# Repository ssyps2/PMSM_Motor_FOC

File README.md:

## Diode Clamped Converter for Vehicle AC machine Drive

### Aim
The aim of this project is to simulate a 3-Phase Diode Clamped Inverter as a battery connected Permanent Magnet Synchronous Machine (PMSM) drive, and design a PCB to implement a low power version of this type of converter. The control algorithm will be tested in PLECS and eventually implemented in the F28379D micro-controller. Torque, speed, and mechanical position closed loop control of the PMSM motor will be included.

### Simulation
The main topology of the circuit for simulation in the PLECS is shown in Figure below.

### PCB Design
The circuit designed in the simulation will be implemented in a 4-layer Printed Circuit Board (PCB). Surface Mount Technology (SMT) will be applied for more compact layout, higher design flexibility, and reducing the noise interference. The microcontroller is selected to be TI’s LAUNCHXL-F28379D, which is a 32-bit MCU with frequency up to 200MHz and sufficient communication interface (like UART, CAN, I2C) and high-speed PWM channels. Also, current sensor will be used to detect the 3-phase current and sampled by ADC to complete the torque control loop.

The schematic of PCB is shown in Figure below.

The PCB layout is shown in Figrue below.

3D Model:

Diode Clamped Inverter:

### TimeTable

### Proposal
[Final Year Project Proposal - Pengyuan SHU.pdf](https://github.com/ssyps2/PMSM_Motor_FOC/files/14595623/Final.Year.Project.Proposal.-.Pengyuan.SHU.pdf)

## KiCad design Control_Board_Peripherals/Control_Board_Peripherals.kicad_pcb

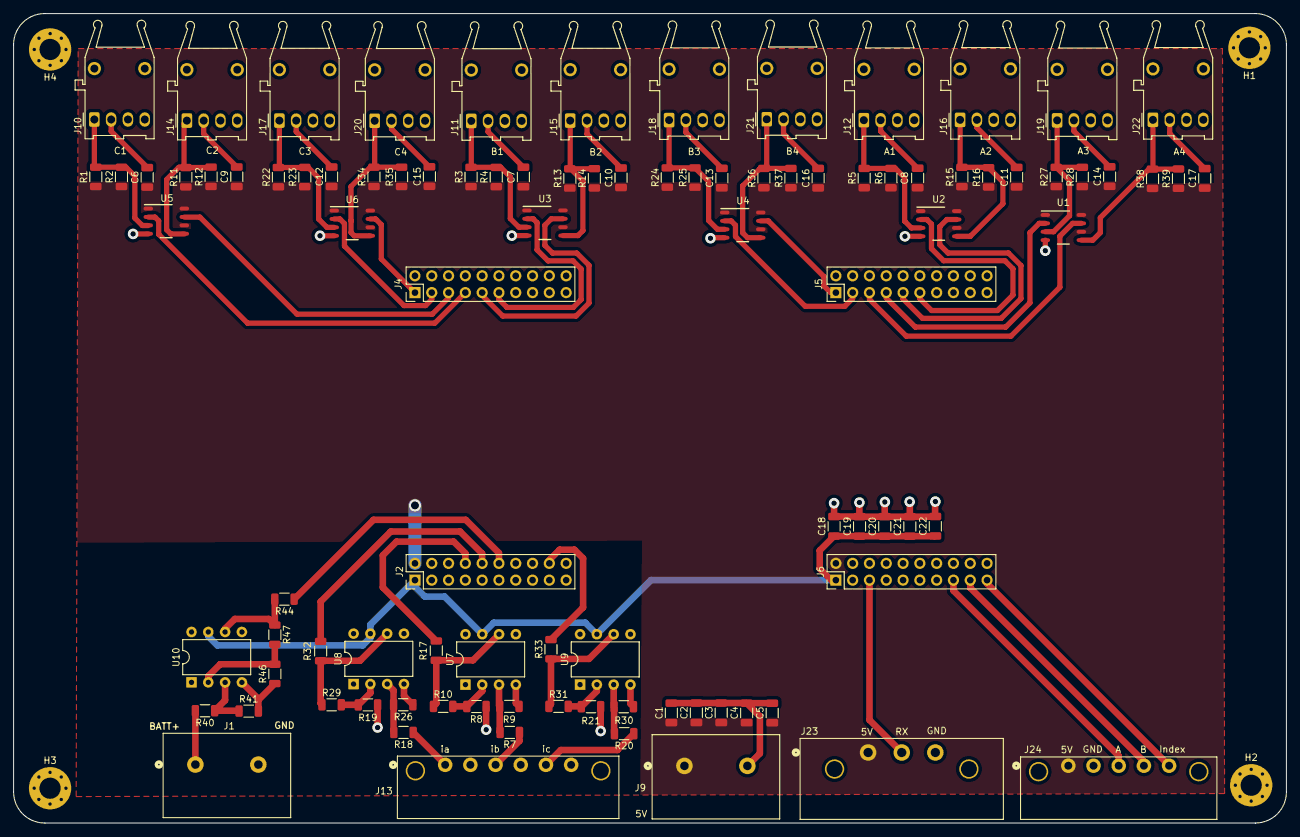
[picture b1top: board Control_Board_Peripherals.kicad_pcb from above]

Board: 2 copper layers, 192.5 x 122.4 mm, 101 parts (0 on the bottom side), 51 nets.

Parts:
C1, C2, C3, C4, C5, C18, C19, C20, C21, C22: 0.1u; C_1206_3216Metric
C6, C7, C8, C9, C10, C11, C12, C13, C14, C15, C16, C17: 4.7u; C_1206_3216Metric
H1, H2, H3, H4: MountingHole; MountingHole_3.2mm_M3_Pad_Via
J1, J9: 1714971; CONN_1714971_PXC
J2, J4, J5, J6: Conn_02x10_Top_Bottom; PinHeader_2x10_P2.54mm_Vertical
J10, J11, J12, J14, J15, J16, J17, J18, J19, J20, J21, J22: HFBR-1521Z; Broadcom_AFBR-16xxZ_Horizontal
J13: 1827907; CONN_1827907
J23: Conn_01x03; CONN_1776511
J24: Conn_01x05; CONN_1827897
R1, R2, R3, R4, R5, R6, R11, R12, R13, R14, R15, R16, R22, R23, R24, R25, R27, R28, R34, R35, R36, R37, R38, R39: 100; R_1206_3216Metric
R7, R18, R20: 5.6k; R_1206_3216Metric
R8, R19, R21: 20k; R_1206_3216Metric
R9, R26, R30: 4.3k; R_1206_3216Metric
R10, R29, R31: 10k; R_1206_3216Metric
R17, R32, R33, R44: 330; R_1206_3216Metric
R40, R46: 100k; R_1206_3216Metric
R41, R47: 1k; R_1206_3216Metric
U1, U2, U3, U4, U5, U6: SN75451BD
U7, U8, U9, U10: TLV2371P; DIP-8_W7.62mm

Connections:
+3.3V: C18.1, C19.1, C20.1, C21.1, C22.1, J2.1, J6.41, U7.7 (V+), U8.7 (V+), U9.7 (V+), U10.7 (V+)
+BATT: J1.1, R40.2
/A1: J5.75, U2.2 (1B)
/A1_In: J12.1 (Data_In), R5.2, R6.2, U2.3 (1Y)
/A2: J5.76, U2.7 (2B)
/A2_In: J16.1 (Data_In), R15.2, R16.2, U2.5 (2Y)
/A3: J5.77, U1.2 (1B)
/A3_In: J19.1 (Data_In), R27.2, R28.2, U1.3 (1Y)
/A4: J5.78, U1.7 (2B)
/A4_In: J22.1 (Data_In), R38.2, R39.2, U1.5 (2Y)
/B1: J4.35 (Pin_5), U3.2 (1B)
/B1_In: J11.1 (Data_In), R3.2, R4.2, U3.3 (1Y)
/B2: J4.36, U3.7 (2B)
/B2_In: J15.1 (Data_In), R13.2, R14.2, U3.5 (2Y)
/B3: J5.79, U4.2 (1B)
/B3_In: J18.1 (Data_In), R24.2, R25.2, U4.3 (1Y)
/B4: J5.80, U4.7 (2B)
/B4_In: J21.1 (Data_In), R36.2, R37.2, U4.5 (2Y)
/C1: J4.37, U5.2 (1B)
/C1_In: J10.1 (Data_In), R1.2, R2.2, U5.3 (1Y)
/C2: J4.38, U5.7 (2B)
/C2_In: J14.1 (Data_In), R11.2, R12.2, U5.5 (2Y)
/C3: J4.39, U6.2 (1B)
/C3_In: J17.1 (Data_In), R22.2, R23.2, U6.3 (1Y)
/C4: J4.40, U6.7 (2B)
/C4_In: J20.1 (Data_In), R34.2, R35.2, U6.5 (2Y)
/CH_A: J6.48, J24.3
/CH_B: J6.49, J24.4
/Index: J6.50, J24.5
/SCIC_RX: J6.43, J23.2
/dc_sample: J2.26, R44.1
/ia_adc: J2.25, R32.1
/ib_adc: J2.24, R17.1
/ic_adc: J2.29, R33.1
GND: C1.2, C2.2, C3.2, C4.2, C5.2, C6.2, C7.2, C8.2, C9.2, C10.2, C11.2, C12.2, C13.2, C14.2, C15.2, C16.2, C17.2, C18.2, C19.2, C20.2, C21.2, C22.2, J1.2, J2.22, J4.20, J5.60, J6.62, J9.2, J10.2 (VEE), J11.2 (VEE), J12.2 (VEE), J13.2, J13.4, J13.6, J14.2 (VEE), J15.2 (VEE), J16.2 (VEE), J17.2 (VEE), J18.2 (VEE), J19.2 (VEE), J20.2 (VEE), J21.2 (VEE), J22.2 (VEE), J23.3, J24.2, R8.2, R9.2, R19.2, R21.2, R26.2, R30.2, R41.2, R46.1, U1.4 (GND), U2.4 (GND), U3.4 (GND), U4.4 (GND), U5.4 (GND), U6.4 (GND), U7.4 (V-), U8.4 (V-), U9.4 (V-), U10.4 (V-)
unnamed: R10.1, R17.2, U7.6
unnamed: R29.1, R32.2, U8.6
unnamed: R31.1, R33.2, U9.6
unnamed: R44.2, R47.1, U10.6
unnamed: R7.2, R9.1, U7.3 (+)
unnamed: R8.1, R10.2, U7.2 (-)
unnamed: R18.2, R26.1, U8.3 (+)
unnamed: R19.1, R29.2, U8.2 (-)
unnamed: R20.2, R30.1, U9.3 (+)
unnamed: R21.1, R31.2, U9.2 (-)
unnamed: R40.1, R41.1, U10.3 (+)
unnamed: R46.2, R47.2, U10.2 (-)
VCC: C1.1, C2.1, C3.1, C4.1, C5.1, C6.1, C7.1, C8.1, C9.1, C10.1, C11.1, C12.1, C13.1, C14.1, C15.1, C16.1, C17.1, J2.21, J6.61, J9.1, J23.1, J24.1, R1.1, R2.1, R3.1, R4.1, R5.1, R6.1, R11.1, R12.1, R13.1, R14.1, R15.1, R16.1, R22.1, R23.1, R24.1, R25.1, R27.1, R28.1, R34.1, R35.1, R36.1, R37.1, R38.1, R39.1, U1.1 (1A), U1.6 (2A), U1.8 (VCC), U2.1 (1A), U2.6 (2A), U2.8 (VCC), U3.1 (1A), U3.6 (2A), U3.8 (VCC), U4.1 (1A), U4.6 (2A), U4.8 (VCC), U5.1 (1A), U5.6 (2A), U5.8 (VCC), U6.1 (1A), U6.6 (2A), U6.8 (VCC)
ia_signal: J13.1, R18.1
ib_signal: J13.3, R7.1
ic_signal: J13.5, R20.1

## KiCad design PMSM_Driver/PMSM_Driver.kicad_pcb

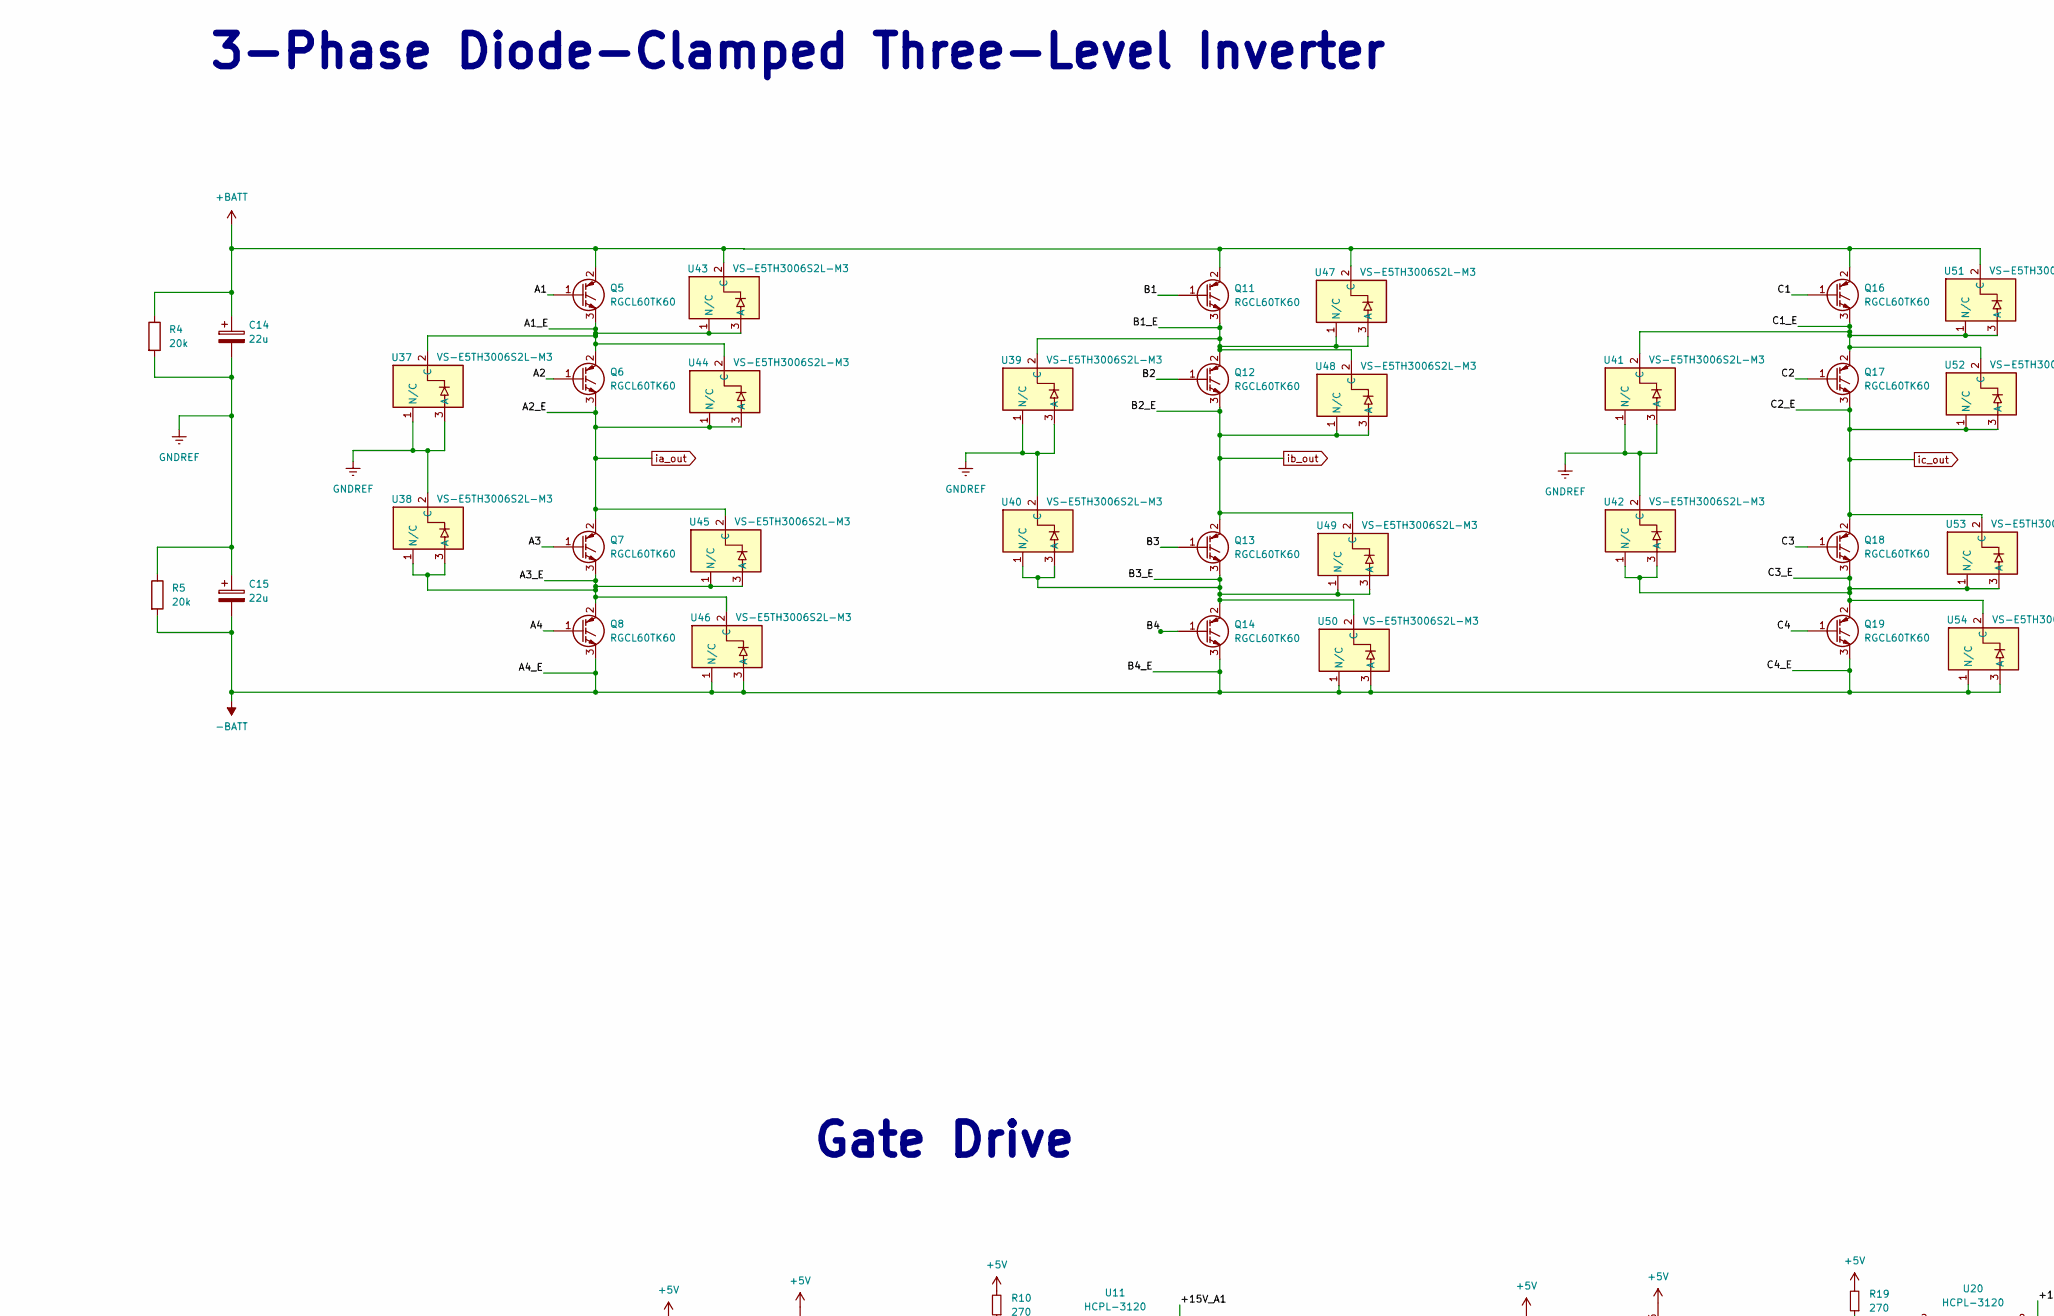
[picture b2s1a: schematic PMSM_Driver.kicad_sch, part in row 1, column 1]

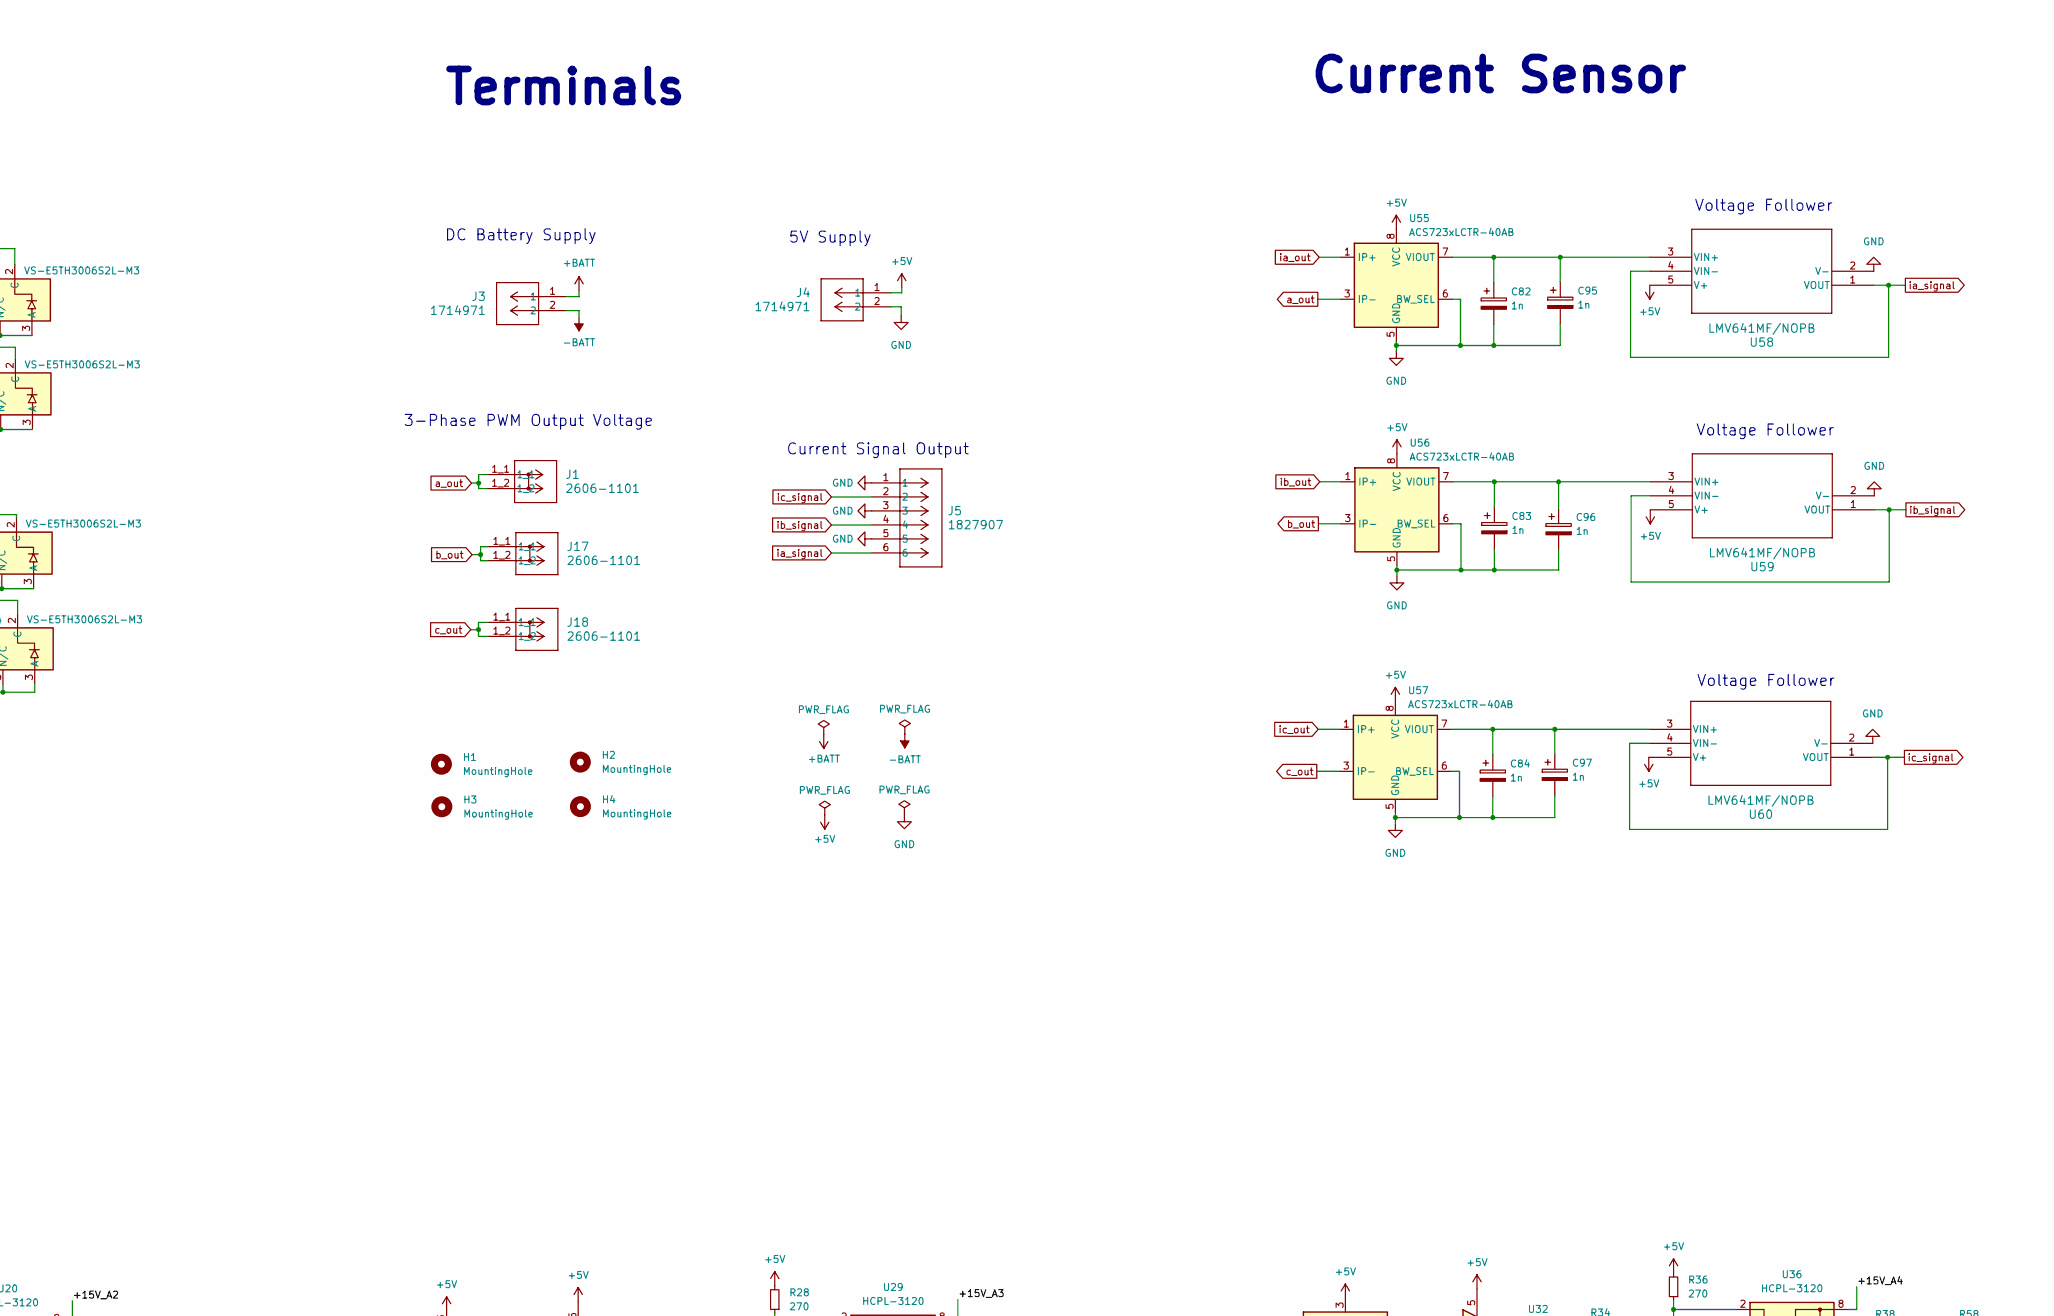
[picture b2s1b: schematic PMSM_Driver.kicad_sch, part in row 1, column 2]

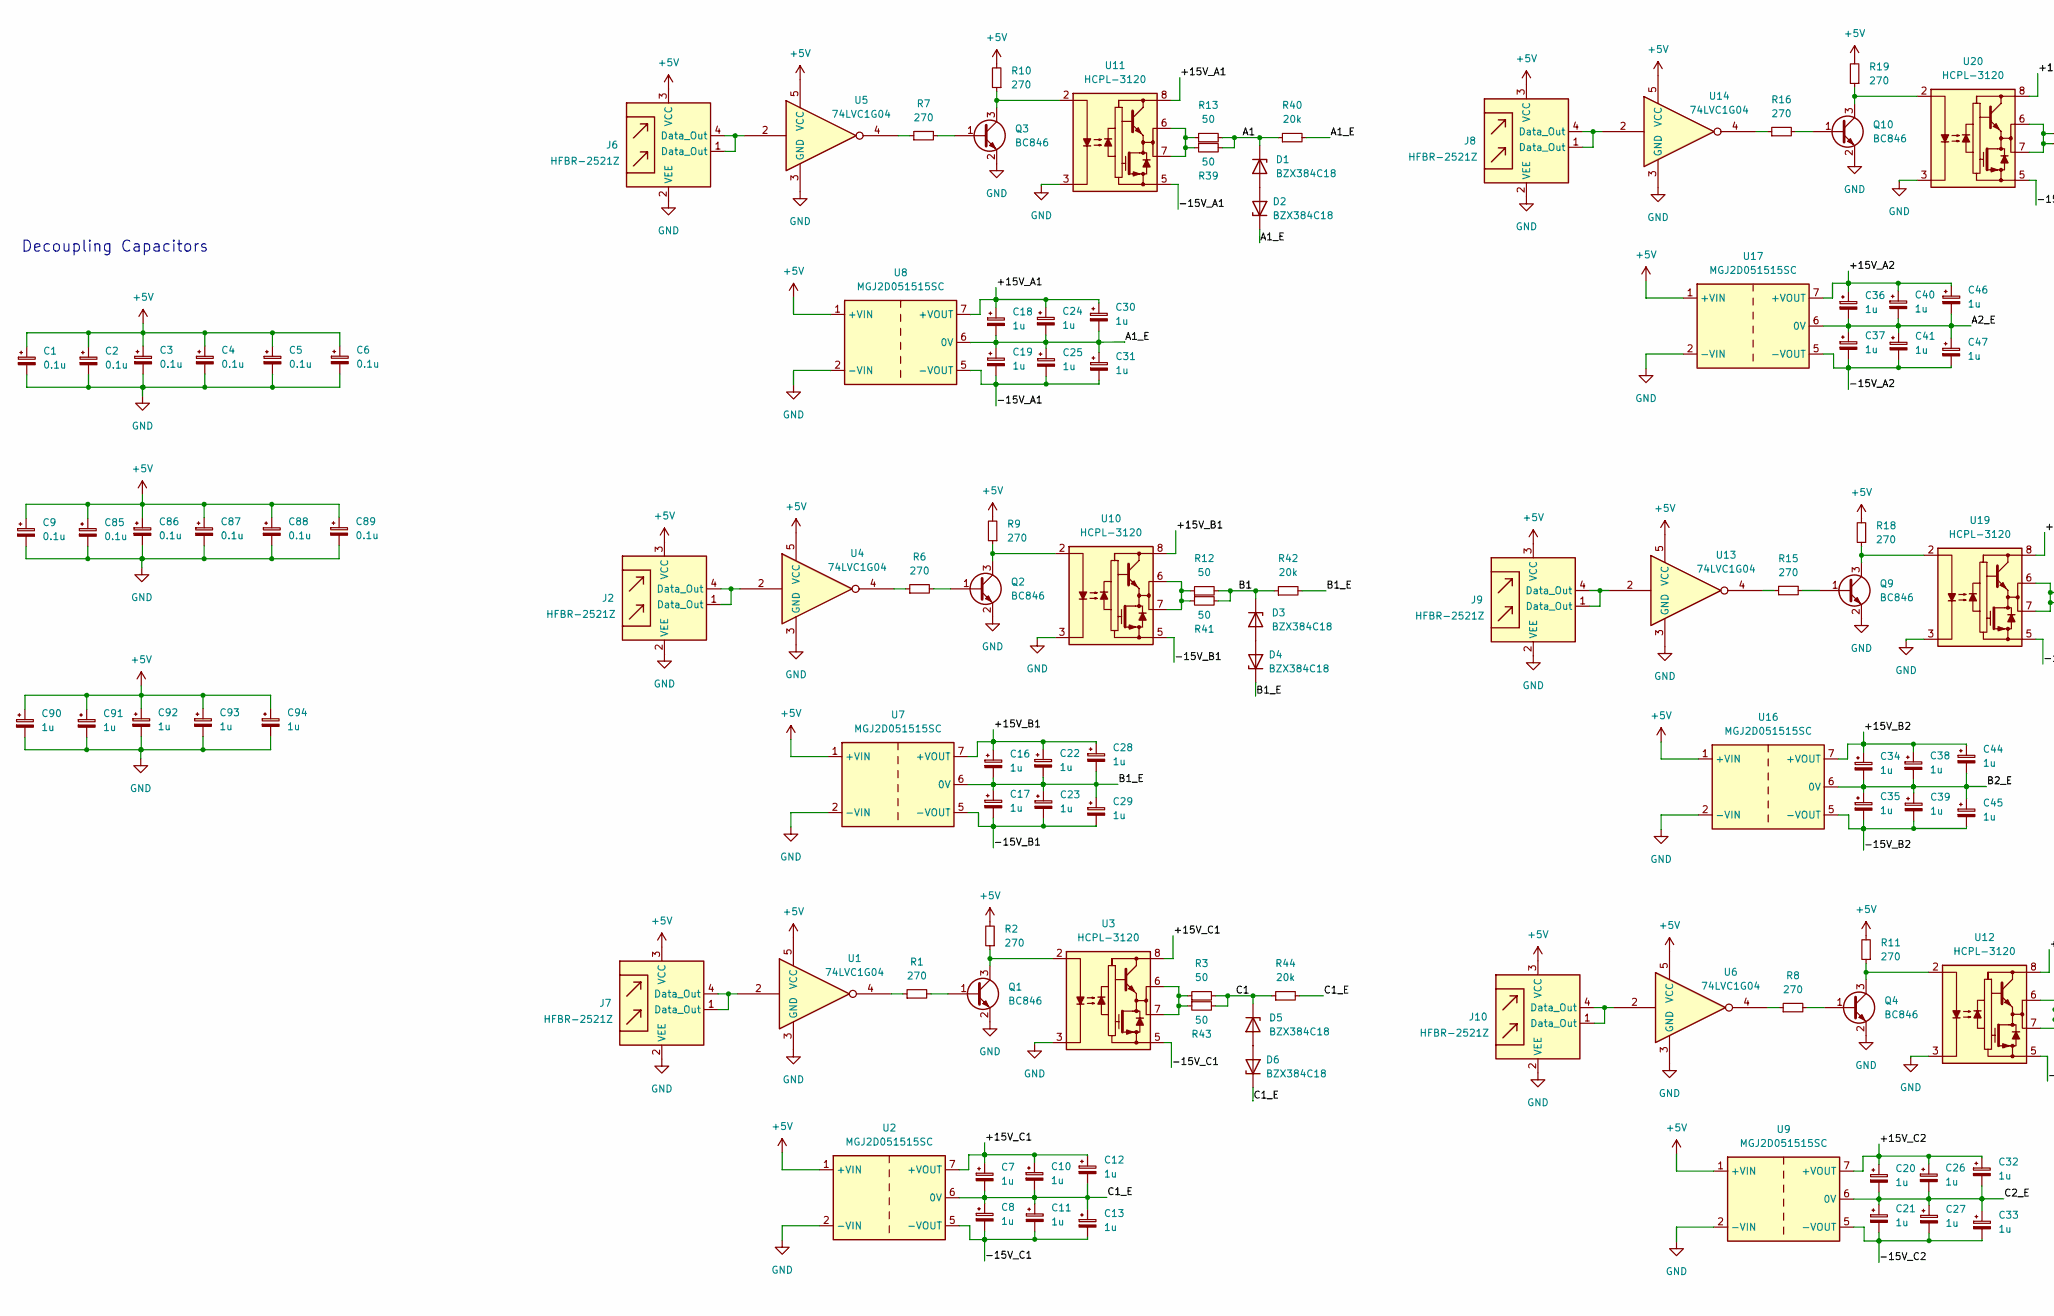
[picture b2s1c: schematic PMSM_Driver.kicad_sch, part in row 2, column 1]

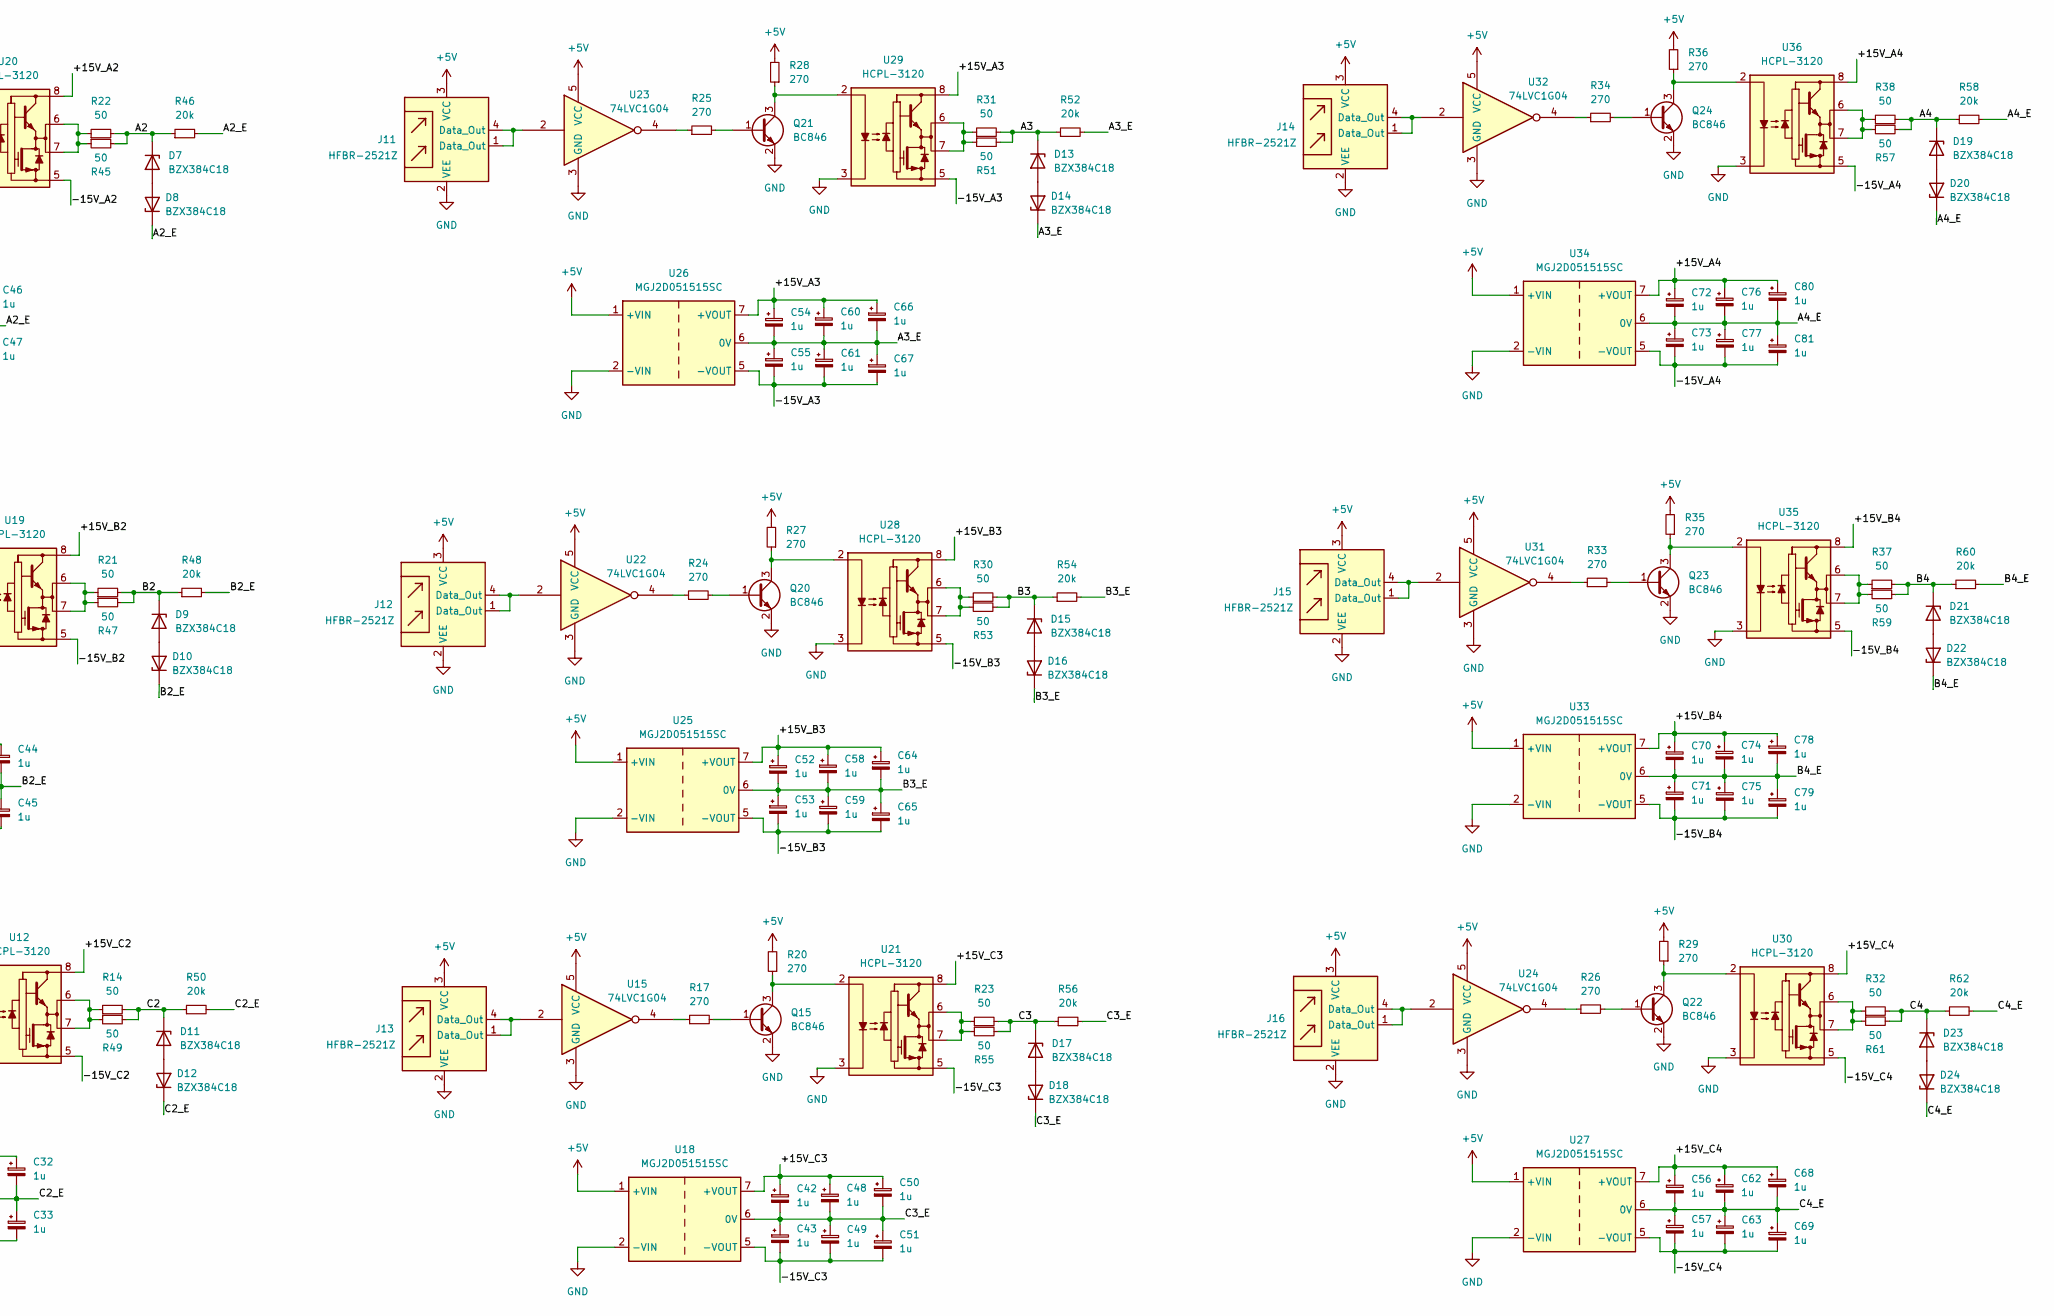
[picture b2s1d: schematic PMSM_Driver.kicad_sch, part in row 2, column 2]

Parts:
C1, C2, C3, C4, C5, C6, C9, C85, C86, C87, C88, C89: 0.1u; C_1206_3216Metric
C7, C8, C10, C11, C12, C13, C16, C17, C18, C19, C20, C21, C22, C23, C24, C25, C26, C27, C28, C29, C30, C31, C32, C33, C34, C35, C36, C37, C38, C39, C40, C41, C42, C43, C44, C45, C46, C47, C48, C49, C50, C51, C52, C53, C54, C55, C56, C57, C58, C59, C60, C61, C62, C63, C64, C65, C66, C67, C68, C69, C70, C71, C72, C73, C74, C75, C76, C77, C78, C79, C80, C81, C90, C91, C92, C93, C94: 1u; C_1206_3216Metric
C14, C15: 22u; CP_Elec_16x17.5
C82, C83, C84, C95, C96, C97: 1n; C_1206_3216Metric
D1, D2, D3, D4, D5, D6, D7, D8, D9, D10, D11, D12, D13, D14, D15, D16, D17, D18, D19, D20, D21, D22, D23, D24: BZX384C18; D_SOD-323
H1, H2, H3, H4: MountingHole; MountingHole_3.2mm_M3_Pad_Via
J1, J17, J18: 2606-1101; CONN_2606-1101_WAG
J2, J6, J7, J8, J9, J10, J11, J12, J13, J14, J15, J16: HFBR-2521Z; Broadcom_AFBR-16xxZ_Horizontal
J3, J4: 1714971; CONN_1714971_PXC
J5: 1827907; CONN_1827907
Q1, Q2, Q3, Q4, Q9, Q10, Q15, Q20, Q21, Q22, Q23, Q24: BC846; SOT-23
Q5, Q6, Q7, Q8, Q11, Q12, Q13, Q14, Q16, Q17, Q18, Q19: RGCL60TK60; TO-3P-3_Vertical
R1, R2, R6, R7, R8, R9, R10, R11, R15, R16, R17, R18, R19, R20, R24, R25, R26, R27, R28, R29, R33, R34, R35, R36: 270; R_1206_3216Metric
R3, R12, R13, R14, R21, R22, R23, R30, R31, R32, R37, R38, R39, R41, R43, R45, R47, R49, R51, R53, R55, R57, R59, R61: 50; R_1206_3216Metric
R4, R5, R40, R42, R44, R46, R48, R50, R52, R54, R56, R58, R60, R62: 20k; R_1206_3216Metric
U1, U4, U5, U6, U13, U14, U15, U22, U23, U24, U31, U32: 74LVC1G04; SOT-23-5
U2, U7, U8, U9, U16, U17, U18, U25, U26, U27, U33, U34: MGJ2D051515SC; Converter_DCDC_Murata_MGJ2DxxxxxxSC_THT
U3, U10, U11, U12, U19, U20, U21, U28, U29, U30, U35, U36: HCPL-3120; DIP-8_W8.89mm_SMDSocket_LongPads
U37, U38, U39, U40, U41, U42, U43, U44, U45, U46, U47, U48, U49, U50, U51, U52, U53, U54: VS-E5TH3006S2L-M3; TO-263-2
U55, U56, U57: ACS723xLCTR-40AB; SOIC-8_3.9x4.9mm_P1.27mm
U58, U59, U60: LMV641MF/NOPB; DBV5_TEX

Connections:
+5V: C1.1, C2.1, C3.1, C4.1, C5.1, C6.1, C9.1, C85.1, C86.1, C87.1, C88.1, C89.1, C90.1, C91.1, C92.1, C93.1, C94.1, J2.3 (VCC), J4.1, J6.3 (VCC), J7.3 (VCC), J8.3 (VCC), J9.3 (VCC), J10.3 (VCC), J11.3 (VCC), J12.3 (VCC), J13.3 (VCC), J14.3 (VCC), J15.3 (VCC), J16.3 (VCC), R2.2, R9.2, R10.2, R11.2, R18.2, R19.2, R20.2, R27.2, R28.2, R29.2, R35.2, R36.2, U1.5 (VCC), U2.1 (+VIN), U4.5 (VCC), U5.5 (VCC), U6.5 (VCC), U7.1 (+VIN), U8.1 (+VIN), U9.1 (+VIN), U13.5 (VCC), U14.5 (VCC), U15.5 (VCC), U16.1 (+VIN), U17.1 (+VIN), U18.1 (+VIN), U22.5 (VCC), U23.5 (VCC), U24.5 (VCC), U25.1 (+VIN), U26.1 (+VIN), U27.1 (+VIN), U31.5 (VCC), U32.5 (VCC), U33.1 (+VIN), U34.1 (+VIN), U55.8 (VCC), U56.8 (VCC), U57.8 (VCC), U58.5 (V+), U59.5 (V+), U60.5 (V+)
+BATT: C14.1, J3.1, Q5.2 (C), Q11.2 (C), Q16.2 (C), R4.1, U43.2 (C), U47.2 (C), U51.2 (C)
-BATT: C15.2, C56.2, C57.1, C62.2, C63.1, C68.2, C69.1, C70.2, C71.1, C72.2, C73.1, C74.2, C75.1, C76.2, C77.1, C78.2, C79.1, C80.2, C81.1, D20.1 (K), D22.1 (K), D24.1 (K), J3.2, Q8.3 (E), Q14.3 (E), Q19.3 (E), R5.2, R58.2, R60.2, R62.2, U27.6 (0V), U33.6 (0V), U34.6 (0V), U46.1 (N/C), U46.3 (A), U50.1 (N/C), U50.3 (A), U54.1 (N/C), U54.3 (A)
/+15V_A1: C18.1, C24.1, C30.1, U8.7 (+VOUT), U11.8 (VCC)
/+15V_A2: C36.1, C40.1, C46.1, U17.7 (+VOUT), U20.8 (VCC)
/+15V_A3: C54.1, C60.1, C66.1, U26.7 (+VOUT), U29.8 (VCC)
/+15V_A4: C72.1, C76.1, C80.1, U34.7 (+VOUT), U36.8 (VCC)
/+15V_B1: C16.1, C22.1, C28.1, U7.7 (+VOUT), U10.8 (VCC)
/+15V_B2: C34.1, C38.1, C44.1, U16.7 (+VOUT), U19.8 (VCC)
/+15V_B3: C52.1, C58.1, C64.1, U25.7 (+VOUT), U28.8 (VCC)
/+15V_B4: C70.1, C74.1, C78.1, U33.7 (+VOUT), U35.8 (VCC)
/+15V_C1: C7.1, C10.1, C12.1, U2.7 (+VOUT), U3.8 (VCC)
/+15V_C2: C20.1, C26.1, C32.1, U9.7 (+VOUT), U12.8 (VCC)
/+15V_C3: C42.1, C48.1, C50.1, U18.7 (+VOUT), U21.8 (VCC)
/+15V_C4: C56.1, C62.1, C68.1, U27.7 (+VOUT), U30.8 (VCC)
/-15V_A1: C19.2, C25.2, C31.2, U8.5 (-VOUT), U11.5 (VEE)
/-15V_A2: C37.2, C41.2, C47.2, U17.5 (-VOUT), U20.5 (VEE)
/-15V_A3: C55.2, C61.2, C67.2, U26.5 (-VOUT), U29.5 (VEE)
/-15V_A4: C73.2, C77.2, C81.2, U34.5 (-VOUT), U36.5 (VEE)
/-15V_B1: C17.2, C23.2, C29.2, U7.5 (-VOUT), U10.5 (VEE)
/-15V_B2: C35.2, C39.2, C45.2, U16.5 (-VOUT), U19.5 (VEE)
/-15V_B3: C53.2, C59.2, C65.2, U25.5 (-VOUT), U28.5 (VEE)
/-15V_B4: C71.2, C75.2, C79.2, U33.5 (-VOUT), U35.5 (VEE)
/-15V_C1: C8.2, C11.2, C13.2, U2.5 (-VOUT), U3.5 (VEE)
/-15V_C2: C21.2, C27.2, C33.2, U9.5 (-VOUT), U12.5 (VEE)
/-15V_C3: C43.2, C49.2, C51.2, U18.5 (-VOUT), U21.5 (VEE)
/-15V_C4: C57.2, C63.2, C69.2, U27.5 (-VOUT), U30.5 (VEE)
/A1: D1.1 (K), Q5.1 (G), R13.2, R39.2, R40.1
/A1_E: C18.2, C19.1, C24.2, C25.1, C30.2, C31.1, D2.1 (K), Q5.3 (E), Q6.2 (C), R40.2, U8.6 (0V), U37.2 (C), U43.1 (N/C), U43.3 (A), U44.2 (C)
/A2: D7.1 (K), Q6.1 (G), R22.2, R45.2, R46.1
/A3: D13.1 (K), Q7.1 (G), R31.2, R51.2, R52.1
/A3_E: C54.2, C55.1, C60.2, C61.1, C66.2, C67.1, D14.1 (K), Q7.3 (E), Q8.2 (C), R52.2, U26.6 (0V), U38.1 (N/C), U38.3 (A), U45.1 (N/C), U45.3 (A), U46.2 (C)
/A4: D19.1 (K), Q8.1 (G), R38.2, R57.2, R58.1
/B1: D3.1 (K), Q11.1 (G), R12.2, R41.2, R42.1
/B1_E: C16.2, C17.1, C22.2, C23.1, C28.2, C29.1, D4.1 (K), Q11.3 (E), Q12.2 (C), R42.2, U7.6 (0V), U39.2 (C), U47.1 (N/C), U47.3 (A), U48.2 (C)
/B2: D9.1 (K), Q12.1 (G), R21.2, R47.2, R48.1
/B3: D15.1 (K), Q13.1 (G), R30.2, R53.2, R54.1
/B3_E: C52.2, C53.1, C58.2, C59.1, C64.2, C65.1, D16.1 (K), Q13.3 (E), Q14.2 (C), R54.2, U25.6 (0V), U40.1 (N/C), U40.3 (A), U49.1 (N/C), U49.3 (A), U50.2 (C)
/B4: D21.1 (K), Q14.1 (G), R37.2, R59.2, R60.1
/C1: D5.1 (K), Q16.1 (G), R3.2, R43.2, R44.1
/C1_E: C7.2, C8.1, C10.2, C11.1, C12.2, C13.1, D6.1 (K), Q16.3 (E), Q17.2 (C), R44.2, U2.6 (0V), U41.2 (C), U51.1 (N/C), U51.3 (A), U52.2 (C)
/C2: D11.1 (K), Q17.1 (G), R14.2, R49.2, R50.1
/C3: D17.1 (K), Q18.1 (G), R23.2, R55.2, R56.1
/C3_E: C42.2, C43.1, C48.2, C49.1, C50.2, C51.1, D18.1 (K), Q18.3 (E), Q19.2 (C), R56.2, U18.6 (0V), U42.1 (N/C), U42.3 (A), U53.1 (N/C), U53.3 (A), U54.2 (C)
/C4: D23.1 (K), Q19.1 (G), R32.2, R61.2, R62.1
GND: C1.2, C2.2, C3.2, C4.2, C5.2, C6.2, C9.2, C82.2, C83.2, C84.2, C85.2, C86.2, C87.2, C88.2, C89.2, C90.2, C91.2, C92.2, C93.2, C94.2, C95.2, C96.2, C97.2, J2.2 (VEE), J4.2, J5.1, J5.3, J5.5, J6.2 (VEE), J7.2 (VEE), J8.2 (VEE), J9.2 (VEE), J10.2 (VEE), J11.2 (VEE), J12.2 (VEE), J13.2 (VEE), J14.2 (VEE), J15.2 (VEE), J16.2 (VEE), Q1.2 (E), Q2.2 (E), Q3.2 (E), Q4.2 (E), Q9.2 (E), Q10.2 (E), Q15.2 (E), Q20.2 (E), Q21.2 (E), Q22.2 (E), Q23.2 (E), Q24.2 (E), U1.3 (GND), U2.2 (-VIN), U3.3 (C), U4.3 (GND), U5.3 (GND), U6.3 (GND), U7.2 (-VIN), U8.2 (-VIN), U9.2 (-VIN), U10.3 (C), U11.3 (C), U12.3 (C), U13.3 (GND), U14.3 (GND), U15.3 (GND), U16.2 (-VIN), U17.2 (-VIN), U18.2 (-VIN), U19.3 (C), U20.3 (C), U21.3 (C), U22.3 (GND), U23.3 (GND), U24.3 (GND), U25.2 (-VIN), U26.2 (-VIN), U27.2 (-VIN), U28.3 (C), U29.3 (C), U30.3 (C), U31.3 (GND), U32.3 (GND), U33.2 (-VIN), U34.2 (-VIN), U35.3 (C), U36.3 (C), U55.5 (GND), U55.6 (BW_SEL), U56.5 (GND), U56.6 (BW_SEL), U57.5 (GND), U57.6 (BW_SEL), U58.2 (V-), U59.2 (V-), U60.2 (V-)
GNDREF: C14.2, C15.1, R4.2, R5.1, U37.1 (N/C), U37.3 (A), U38.2 (C), U39.1 (N/C), U39.3 (A), U40.2 (C), U41.1 (N/C), U41.3 (A), U42.2 (C)
unnamed: D1.2 (A), D2.2 (A)
unnamed: D3.2 (A), D4.2 (A)
unnamed: D5.2 (A), D6.2 (A)
unnamed: D7.2 (A), D8.2 (A)
unnamed: D9.2 (A), D10.2 (A)
unnamed: D11.2 (A), D12.2 (A)
unnamed: D13.2 (A), D14.2 (A)
unnamed: D15.2 (A), D16.2 (A)
unnamed: D17.2 (A), D18.2 (A)
unnamed: D19.2 (A), D20.2 (A)
unnamed: D21.2 (A), D22.2 (A)
unnamed: D23.2 (A), D24.2 (A)
unnamed: J2.1 (Data_Out), J2.4 (Data_Out), U4.2
unnamed: J6.1 (Data_Out), J6.4 (Data_Out), U5.2
unnamed: J7.1 (Data_Out), J7.4 (Data_Out), U1.2
unnamed: J8.1 (Data_Out), J8.4 (Data_Out), U14.2
unnamed: J9.1 (Data_Out), J9.4 (Data_Out), U13.2
unnamed: J10.1 (Data_Out), J10.4 (Data_Out), U6.2
unnamed: J11.1 (Data_Out), J11.4 (Data_Out), U23.2
unnamed: J12.1 (Data_Out), J12.4 (Data_Out), U22.2
unnamed: J13.1 (Data_Out), J13.4 (Data_Out), U15.2
unnamed: J14.1 (Data_Out), J14.4 (Data_Out), U32.2
unnamed: J15.1 (Data_Out), J15.4 (Data_Out), U31.2
unnamed: J16.1 (Data_Out), J16.4 (Data_Out), U24.2
unnamed: Q1.1 (B), R1.2
unnamed: Q1.3 (C), R2.1, U3.2 (A)
unnamed: Q2.1 (B), R6.2
unnamed: Q2.3 (C), R9.1, U10.2 (A)
unnamed: Q3.1 (B), R7.2
unnamed: Q3.3 (C), R10.1, U11.2 (A)
unnamed: Q4.1 (B), R8.2
unnamed: Q4.3 (C), R11.1, U12.2 (A)
unnamed: Q9.1 (B), R15.2
unnamed: Q9.3 (C), R18.1, U19.2 (A)
unnamed: Q10.1 (B), R16.2
unnamed: Q10.3 (C), R19.1, U20.2 (A)
unnamed: Q15.1 (B), R17.2
unnamed: Q15.3 (C), R20.1, U21.2 (A)
unnamed: Q20.1 (B), R24.2
unnamed: Q20.3 (C), R27.1, U28.2 (A)
unnamed: Q21.1 (B), R25.2
unnamed: Q21.3 (C), R28.1, U29.2 (A)
unnamed: Q22.1 (B), R26.2
unnamed: Q22.3 (C), R29.1, U30.2 (A)
unnamed: Q23.1 (B), R33.2
unnamed: Q23.3 (C), R35.1, U35.2 (A)
unnamed: Q24.1 (B), R34.2
unnamed: Q24.3 (C), R36.1, U36.2 (A)
unnamed: R1.1, U1.4
unnamed: R3.1, R43.1, U3.6 (VO), U3.7 (VO)
unnamed: R6.1, U4.4
unnamed: R7.1, U5.4
unnamed: R8.1, U6.4
unnamed: R12.1, R41.1, U10.6 (VO), U10.7 (VO)
unnamed: R13.1, R39.1, U11.6 (VO), U11.7 (VO)
unnamed: R14.1, R49.1, U12.6 (VO), U12.7 (VO)
unnamed: R15.1, U13.4
unnamed: R16.1, U14.4
unnamed: R17.1, U15.4
unnamed: R21.1, R47.1, U19.6 (VO), U19.7 (VO)
unnamed: R22.1, R45.1, U20.6 (VO), U20.7 (VO)
unnamed: R23.1, R55.1, U21.6 (VO), U21.7 (VO)
unnamed: R24.1, U22.4
unnamed: R25.1, U23.4
unnamed: R26.1, U24.4
unnamed: R30.1, R53.1, U28.6 (VO), U28.7 (VO)
unnamed: R31.1, R51.1, U29.6 (VO), U29.7 (VO)
unnamed: R32.1, R61.1, U30.6 (VO), U30.7 (VO)
unnamed: R33.1, U31.4
unnamed: R34.1, U32.4
unnamed: R37.1, R59.1, U35.6 (VO), U35.7 (VO)
unnamed: R38.1, R57.1, U36.6 (VO), U36.7 (VO)
unnamed: C82.1, C95.1, U55.7 (VIOUT), U58.3 (VIN+)
unnamed: C83.1, C96.1, U56.7 (VIOUT), U59.3 (VIN+)
unnamed: C84.1, C97.1, U57.7 (VIOUT), U60.3 (VIN+)
a_out: J1.1_1, J1.1_2, U55.3 (IP-), U55.4 (IP-)
b_out: J17.1_1, J17.1_2, U56.3 (IP-), U56.4 (IP-)
c_out: J18.1_1, J18.1_2, U57.3 (IP-), U57.4 (IP-)
ia_out: C36.2, C37.1, C40.2, C41.1, C46.2, C47.1, D8.1 (K), Q6.3 (E), Q7.2 (C), R46.2, U17.6 (0V), U44.1 (N/C), U44.3 (A), U45.2 (C), U55.1 (IP+), U55.2 (IP+)
ia_signal: J5.6, U58.1 (VOUT), U58.4 (VIN-)
ib_out: C34.2, C35.1, C38.2, C39.1, C44.2, C45.1, D10.1 (K), Q12.3 (E), Q13.2 (C), R48.2, U16.6 (0V), U48.1 (N/C), U48.3 (A), U49.2 (C), U56.1 (IP+), U56.2 (IP+)
ib_signal: J5.4, U59.1 (VOUT), U59.4 (VIN-)
ic_out: C20.2, C21.1, C26.2, C27.1, C32.2, C33.1, D12.1 (K), Q17.3 (E), Q18.2 (C), R50.2, U9.6 (0V), U52.1 (N/C), U52.3 (A), U53.2 (C), U57.1 (IP+), U57.2 (IP+)
ic_signal: J5.2, U60.1 (VOUT), U60.4 (VIN-)

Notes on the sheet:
Voltage Follower
Gate Drive
3-Phase Diode-Clamped Three-Level Inverter
Terminals
DC Battery Supply
Decoupling Capacitors
5V Supply
Current Signal Output
3-Phase PWM Output Voltage
Current Sensor

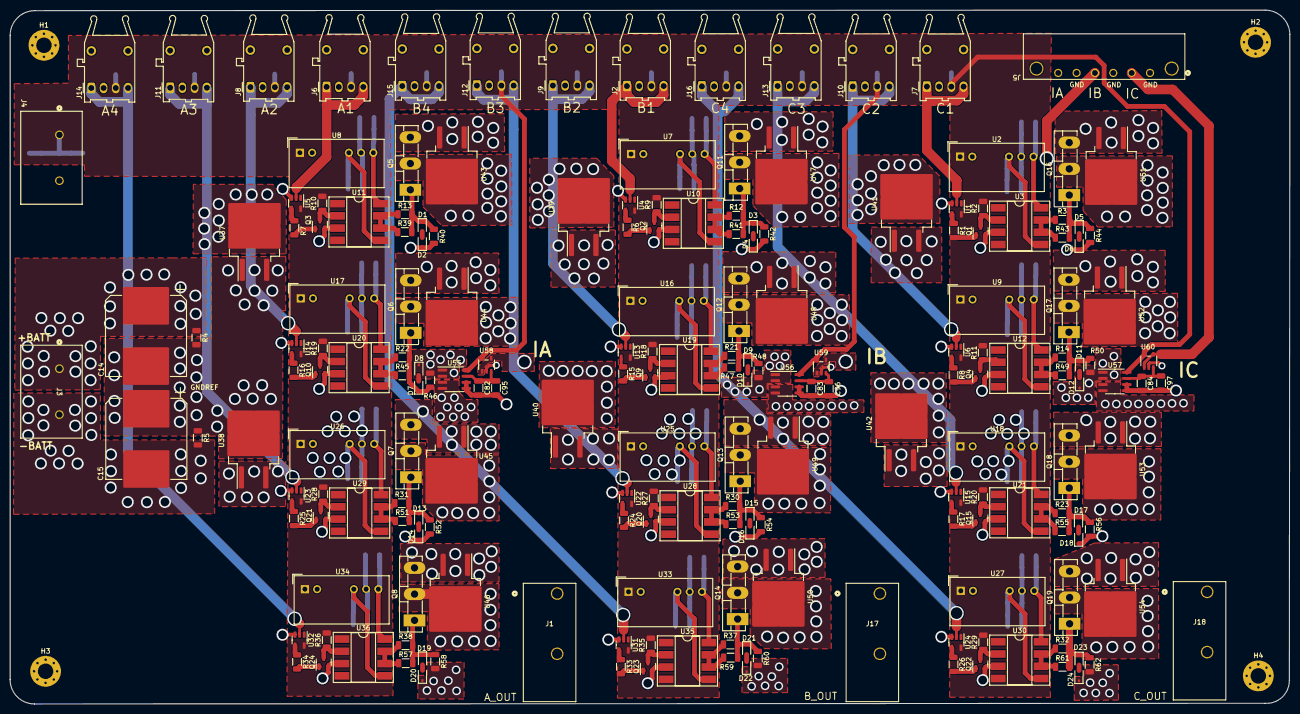
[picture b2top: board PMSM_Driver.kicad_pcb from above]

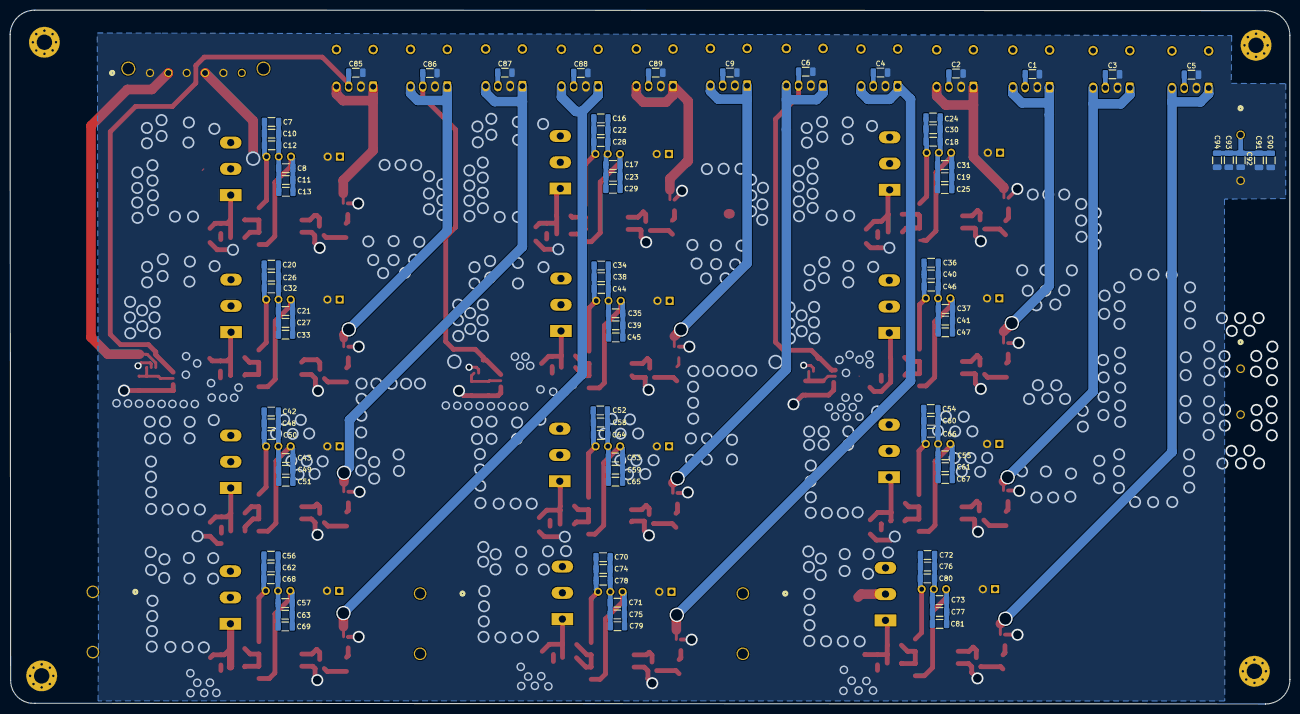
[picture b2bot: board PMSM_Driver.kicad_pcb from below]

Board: 4 copper layers, 265.6 x 144.0 mm, 289 parts (89 on the bottom side), 131 nets.
